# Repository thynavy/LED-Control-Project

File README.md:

# LED Control Project Using 74HC595 Shift Register and 555 Timer

## Project Overview

This project demonstrates controlling multiple LEDs using a 74HC595 shift register driven by a 555 timer. The 74HC595 allows for efficient expansion of output pins, letting you control multiple LEDs with only a few microcontroller or timer connections. Using the 555 timer as a clock source, this circuit sequentially shifts bits through the shift register, enabling a visual LED pattern.

This project is ideal for learning about shift registers, basic timing circuits, and efficient LED control with minimal I/O usage.

<p align="center">
    
    <br />
    <strong>Figure 1: LED Control Project Using 74HC595 Shift Register and 555 Timer</strong>
</p>

## Features

- Efficient LED Control: Controls multiple LEDs using only three control pins through the 74HC595 shift register.
- Clocked by 555 Timer: Uses a 555 timer IC to generate a steady clock pulse that shifts data through the register, producing an LED sequence.
- Scalable Design: Additional 74HC595 ICs can be chained together to control even more LEDs.

## Components

1. 74HC595 Shift Register - 1x (expandable with additional ICs if more LEDs are needed)
2. 555 Timer - 1x, configured to produce clock pulses
3. LEDs - Number varies depending on the project (typically 8 per 74HC595)
4. Resistors - For LED current limiting and setting 555 timer frequency
5. Capacitors - For stabilizing the 555 timer
6. Potentiometer - Optional, for adjusting the frequency of the 555 timer
7. Breadboard and Jumper Wires
8. Power Supply - 5V or other suitable voltage, depending on LED and IC specifications

## Circuit Diagram

**Note:** [_The circuit diagram (PDF)_](https://github.com/thynavy/LED_Control_Project_Using_74HC595/blob/main/Schematic.pdf) This circuit shows the 555 timer in astable mode, generating clock pulses for the 74HC595 shift register, which sequentially lights up LEDs connected to its output pins.

## How It Works

1. Clock Pulse Generation with 555 Timer:
    - The 555 timer is configured in astable mode to produce a continuous clock signal. Adjusting resistor and capacitor values (or using a potentiometer) can vary the pulse frequency, changing the speed of the LED sequence.
2. Shift Register Operation with 74HC595:
    - The 74HC595 shift register takes the data input on its SER (Serial Data) pin, shifts the data with each clock pulse, and outputs it across QA to QD pins.
    - The SRCLK (Shift Register Clock) pin is connected to the 555 timer’s output, which shifts the bits through the register on each pulse.
    - The RCLK (Register Clock/Latch) pin updates the output pins, showing the new data pattern on the LEDs.
3. LED Control:
    - LEDs connected to QA to QD of the 74HC595 display a pattern depending on the data shifted through the register.
    - Using specific binary data sequences, you can create various LED effects, like a “chase” effect, where each LED lights up in sequence.

## Setup and Usage

1. Circuit Assembly:
    - Place the 74HC595 shift register and 555 timer ICs on a board.
    - Connect the LEDs to the output pins (QA to QD) of the 74HC595, with current-limiting resistors in series to protect the LEDs.
2. Data Loading:
    - Use a microcontroller or manually toggle the data line to the 74HC595’s SER pin to control the bit pattern. This can also be automated with additional 555 or logic circuitry.
3. Power Up and Adjust:
    - Connect a 5V-9V power supply (or as required by the components) and power the circuit.
    - Adjust the potentiometer (if used) to control the speed of the LED sequence.

## Example Applications

This project is suitable for:
  - Learning how to use shift registers and save GPIO pins.
  - Creating visual LED patterns, chaser lights, or other dynamic light displays.
  - Experimenting with clocked and timed circuits.

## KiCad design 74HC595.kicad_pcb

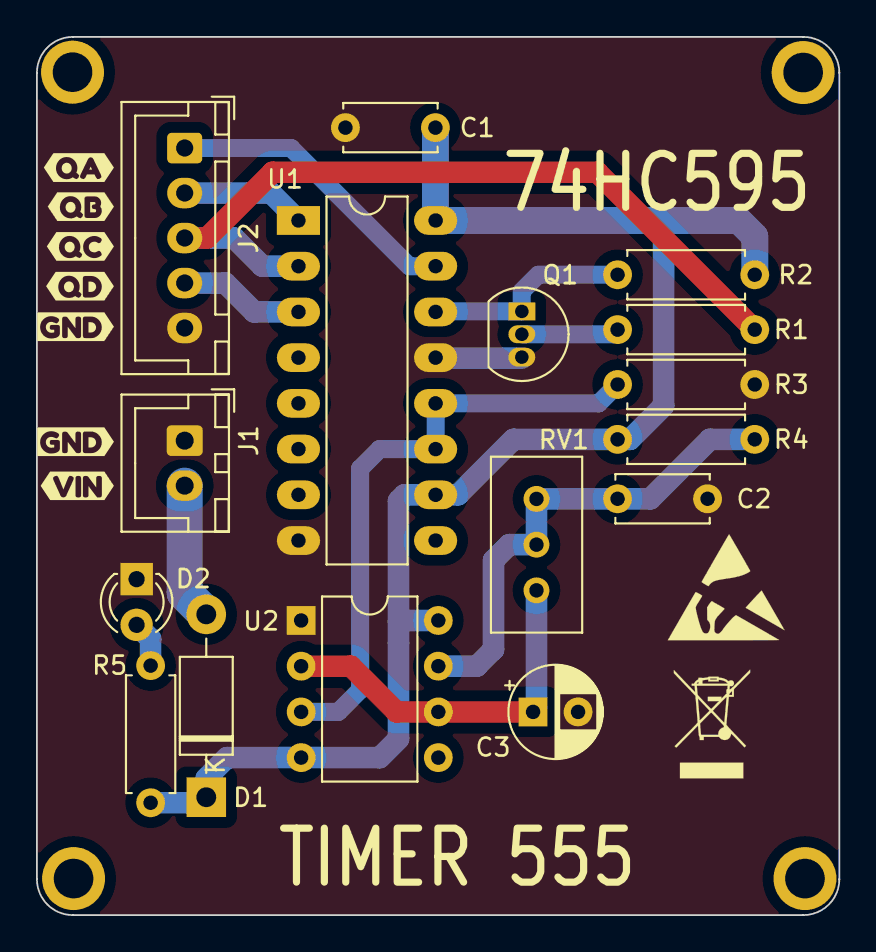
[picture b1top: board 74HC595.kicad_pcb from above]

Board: 2 copper layers, 44.6 x 48.8 mm, 23 parts (0 on the bottom side), 13 nets.

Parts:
C1, C2: 0.1UF; C_Disc_D5.0mm_W2.5mm_P5.00mm
C3: 100UF; CP_Radial_D5.0mm_P2.50mm
D1: 1N4007; D_DO-41_SOD81_P10.16mm_Horizontal
D2: LED; LED_D3.0mm
J1: Conn_01x02_Female; JST_XH_B2B-XH-A_1x02_P2.50mm_Vertical
J2: Conn_01x05_Female; JST_XH_B5B-XH-A_1x05_P2.50mm_Vertical
Q1: BC547; TO-92_Inline
R1, R2, R3, R4: 10K; R_Axial_DIN0207_L6.3mm_D2.5mm_P7.62mm_Horizontal
R5: 330; R_Axial_DIN0207_L6.3mm_D2.5mm_P7.62mm_Horizontal
RV1: 10K; Potentiometer_Bourns_3296W_Vertical
U1: 74HC595; DIP-16_W7.62mm_LongPads
U2: NE555P; DIP-8_W7.62mm
kibuzzard-672B08B6: G***; kibuzzard-672B08B6
kibuzzard-672B08D5: G***; kibuzzard-672B08D5
kibuzzard-672B08DC: G***; kibuzzard-672B08DC
kibuzzard-672B084F: G***; kibuzzard-672B084F
kibuzzard-672B089F: G***; kibuzzard-672B089F
kibuzzard-672B0886: G***; kibuzzard-672B0886
kibuzzard-672B0903: G***; kibuzzard-672B0903

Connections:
+9V: C1.1, D1.1 (K), R2.2, R4.2, R5.2, U1.10 (~SRCLR), U1.16 (VCC), U2.4 (R), U2.8 (VCC)
/Q: R3.2, U1.11 (SRCLK), U1.12 (RCLK), U2.3 (Q)
/QA: J2.1, U1.15 (QA)
/QB: J2.2, U1.1 (QB)
/QC: J2.3, R1.1, U1.2 (QC)
/QD: J2.4, U1.3 (QD)
/SER: Q1.1 (C), R2.1, U1.14 (SER)
/TR: C3.1, RV1.3, U2.2 (TR), U2.6 (THR)
GND: C1.2, C2.2, C3.2, D2.1 (K), J1.1, J2.5, Q1.3 (E), R3.1, U1.8 (GND), U1.13 (~OE), U2.1 (GND)
unnamed: C2.1, R4.1, RV1.1, RV1.2, U2.7 (DIS)
unnamed: D1.2 (A), J1.2
unnamed: D2.2 (A), R5.1
unnamed: Q1.2 (B), R1.2

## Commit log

2024-11-12 schematic update
